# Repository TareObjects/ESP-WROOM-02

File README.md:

# ESP-WROOM-02
ESP-WROOM-02関連の基板設計とソフトウェアをまとめておきます。

サポートページはこちら：http://jiwashin.blogspot.com/p/esp-wroom-02-board1.html

# Eagle下のプロダクツ

## Board1
ESP-WROOM-02と安定化電源を搭載した標準基板です。「さくっと使えるESP-WROOM-02基板」がコンセプトです。

## Board1 DustCounter
Board1をベースにして、ダストカウンターPPD42とOLED（I2c, 0.96インチのあれ）を簡単に接続して使えるようにしました。
https://gist.github.com/TareObjects/b11eb0981f3f318fd35e

# Arduino下のプロジェクト

## ESP_NOW_ADC / ESP_NOW_DAC / ESP_UDP_ADC / ESP_UDP_DAC
WiFiワイアレスオーディオをESPで廉価に実現しようとしたもののADC/DACとのやりとりがNOW/UDPの処理に邪魔されてしまい信号波形が崩れてしまい、挫折。ADCはMCP3204、DACはMCP4922を使っていますので、そっち方面の参考にしていただければ幸いです。

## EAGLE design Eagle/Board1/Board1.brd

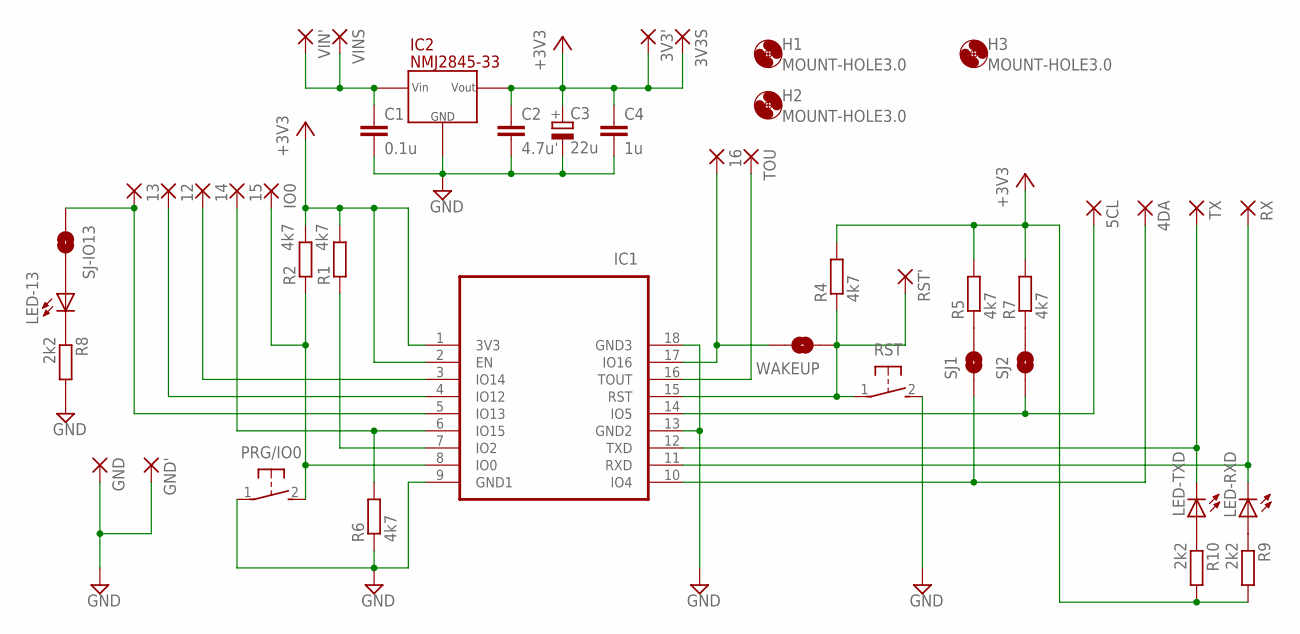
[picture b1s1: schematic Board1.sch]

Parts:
3V3', 3V3S, 4DA, 5CL, 12, 13, 14, 15, 16: 1,6/0,8
C1: 0.1u; C0603
C2: 4.7u; C0805
C3: 22u; C6
C4: 1u; C0603
GND: 1,6/0,8
GND': 1,6/0,8
H1, H2, H3: MOUNT-HOLE3.0; 3,0
IC1: ESP-WROOM-02FRONT-FACE; FRONT-FACE
IC2: NMJ2845-33; TO-252-3
IO0: 1,6/0,8
LED-13: IO13; CHIP-LED0603
LED-RXD: R; CHIP-LED0603
LED-TXD: T; CHIP-LED0603
PRG/IO0: SWITCH-TACTILESW; SWITCH-TACTILE
R1, R2, R4, R5, R6, R7: 4k7; R0603
R8, R9, R10: 2k2; R0603
RST: SWITCH-TACTILESW; SWITCH-TACTILE
RST': 1,6/0,8
RX: 1,6/0,8
SJ1: SDA/PU; SJ_2S-NO
SJ2: SCL/PU; SJ_2S-NO
SJ-IO13: SOLDERJUMPERNO; SJ_2S-NO
TOU: 1,6/0,8
TX: 1,6/0,8
VIN': 1,6/0,8
VINS: 1,6/0,8
WAKEUP: SOLDERJUMPERNO; SJ_2S-NO

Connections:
+3V3: 3V3'.1, 3V3S.1, C2.1, C3.+, C4.1, IC1.1 (3V3), IC1.2 (EN), IC2.VOUT, R1.2, R2.2, R4.2, R5.2, R7.2, R9.2, R10.2
GND: C1.2, C2.2, C3.-, C4.2, GND.1, GND'.1, IC1.9 (GND1), IC1.13 (GND2), IC1.18 (GND3), IC2.GND, PRG/IO0.1, R6.1, R8.2, RST.2
unnamed: IC1.8 (IO0), IO0.1, PRG/IO0.2, R2.1
unnamed: IC1.7 (IO2), R1.1
unnamed: 4DA.1, IC1.10 (IO4), SJ1.1
unnamed: IC1.11 (RXD), LED-RXD.C, RX.1
unnamed: IC1.12 (TXD), LED-TXD.C, TX.1
unnamed: 5CL.1, IC1.14 (IO5), SJ2.1
unnamed: IC1.15 (RST), R4.1, RST.1, RST'.1, WAKEUP.1
unnamed: IC1.16 (TOUT), TOU.1
unnamed: 16.1, IC1.17 (IO16), WAKEUP.2
unnamed: R5.1, SJ1.2
unnamed: R7.1, SJ2.2
unnamed: 14.1, IC1.3 (IO14)
unnamed: 15.1, IC1.6 (IO15), R6.2
unnamed: 12.1, IC1.4 (IO12)
unnamed: 13.1, IC1.5 (IO13), SJ-IO13.1
unnamed: C1.1, IC2.VIN, VIN'.1, VINS.1
unnamed: LED-13.A, SJ-IO13.2
unnamed: LED-13.C, R8.1
unnamed: LED-TXD.A, R10.1
unnamed: LED-RXD.A, R9.1

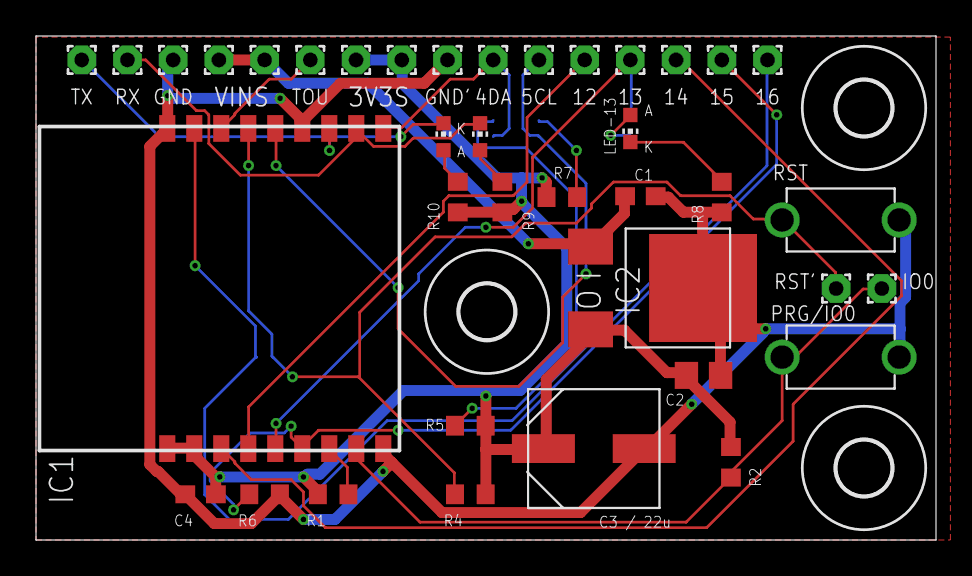
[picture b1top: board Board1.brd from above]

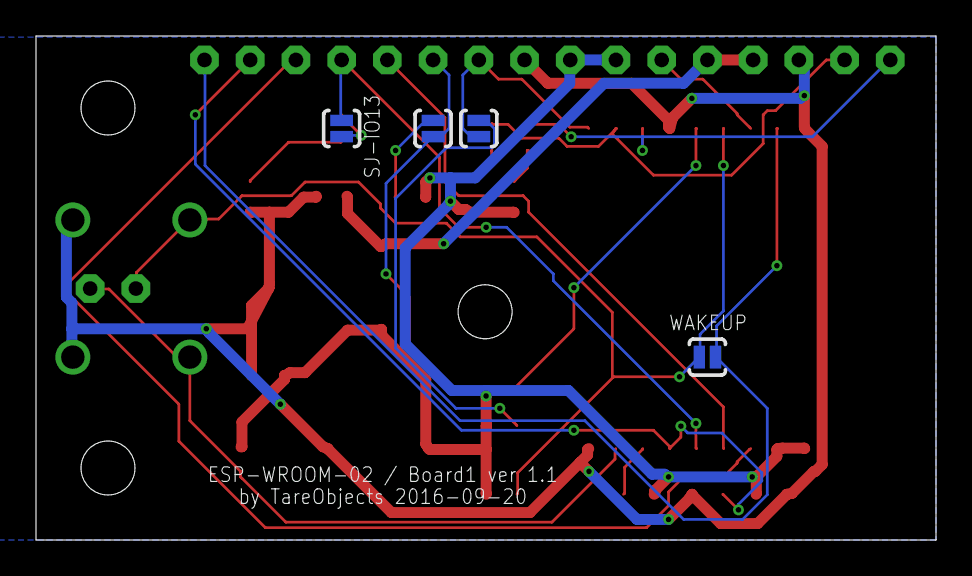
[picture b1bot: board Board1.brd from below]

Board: 2 copper layers, 50.0 x 28.0 mm, 45 parts (4 on the bottom side), 22 nets.

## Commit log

2016-04-10 製品発売にともない最初のコミット
2016-04-24 動かなかったけど、なんかの参考になれば
2016-05-06 公開 「できるだけ小さいESP-WROOM-02ブレイクアウト基板」として開発していましたが、ESP8285という5x5mmサイズの後継機（中身はほぼ同じ、フラッシュが1MBに縮小）が発売になるので、ボツ。
2016-06-24 STTS751温度センサー用ライブラリ
2016-06-25 ディレクトリ移動
2016-06-25 独立したリポジトリに移動
2016-07-01 Ambientへの書き込みがとりあえず動いたのでコミット。 ToDo : 掃除 ToDo : RTC RX8025のライブラリ化
2016-07-05 気圧データをfloatに変換 ・ただしArduinoJSONが指数形式に変換してしまうため、Pa単位（標準気圧＝101.3Pa）の少数形式に変更
2016-07-06 気圧の単位を変更、その他バグフィックス
2016-10-22 一旦没にしてましたが発売することになり復活 ・シルクを整理 ・EN端子やLEDの電流制限抵抗値を見直し
2016-11-03 ver 1.1 : EN直結, RESET/PROG端子追加 - ENのプルアップ抵抗をやめてVcc直結 - RESET/PROGのPADを追加

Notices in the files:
parts and their libraries:
SparkFun: Licensing: CC v3.0 Share-Alike You are welcome to use this library for commercial purposes.
